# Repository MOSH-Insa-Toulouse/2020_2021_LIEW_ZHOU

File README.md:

# TP MOSH Gas Sensor Application using LoRa Communication
This project is done in conjunction with the Smart Devices module. The objective of this project is to develop an application that acts as a breathalyser, detecting alcohol and send a warning to, for example, a web application. The communication from the sensor node to that web application was done through The Things Network platform via LoRa. We created a graphical interface at Node-RED to visualise the gas sensor value.

## Arduino
For the prototyping on Arduino, we did not use the gas sensor fabricated at the cleanroom but a similar one, namely, MQ3. For energy efficiency purpose, we put the mcu to sleep when no alcohol is detected, and only wake up and transmit using LoRa when alcohol is detected (gas sensor value exceeds a certain threshold).

### Materials

Following is a list of the components used:
* Arduino Uno x 1 
* RN2483A LoRa module x 1
* LED x 1
* Gas sensor MQ3 x 1

### LoRa Communication through TTN

### Graphical Interface (Node-RED)

## Datasheet
Click [here](https://github.com/MOSH-Insa-Toulouse/2020_2021_LIEW_ZHOU/blob/main/Datasheet.pdf) to see the datasheet we created for the gas sensor we fabricated at the cleanroom training. 

## KiCad - Shield for Arduino

### TODO design an electronic card with Kicad
- [x] Creat Kicad porject(Gas_sensor_shield)
- [x] Design the circuit board
- [x] Verification of electrical tests **ERC**
- [x] Association of component footprints with their case
- [x] Netlist generation
- [x] Design of the electronic card
- [x] Importing the netlist
- [x] Component placement
- [x] Define the design constraints of the electronic board ([stackup](https://www.emsproto.com/fr/standard-multi-layer-pcb-stackup))
- [x] Route the tracks of the electronic board

### Schematic

### Placement and Routing

### 3D View

## LTSpice
### Objective
This gas sensor gives an output of around 100 nA. This is not acceptable for normal microcontrollers used nowadays. Therefore, to obtain the output of the gas sensor, the following circuit is needed as an intermediate between the gas sensor and the ADC of  a microcontroller. This circuit will give a gain of 100 in nominal condition.

## Contribution
### Students 
* Terence Chun Heng LIEW
* Zheng ZHOU
### Tutors
* Jérémie GRISOLIA
* Arnauld BIGANZOLI 
* Benjamin MESTRE

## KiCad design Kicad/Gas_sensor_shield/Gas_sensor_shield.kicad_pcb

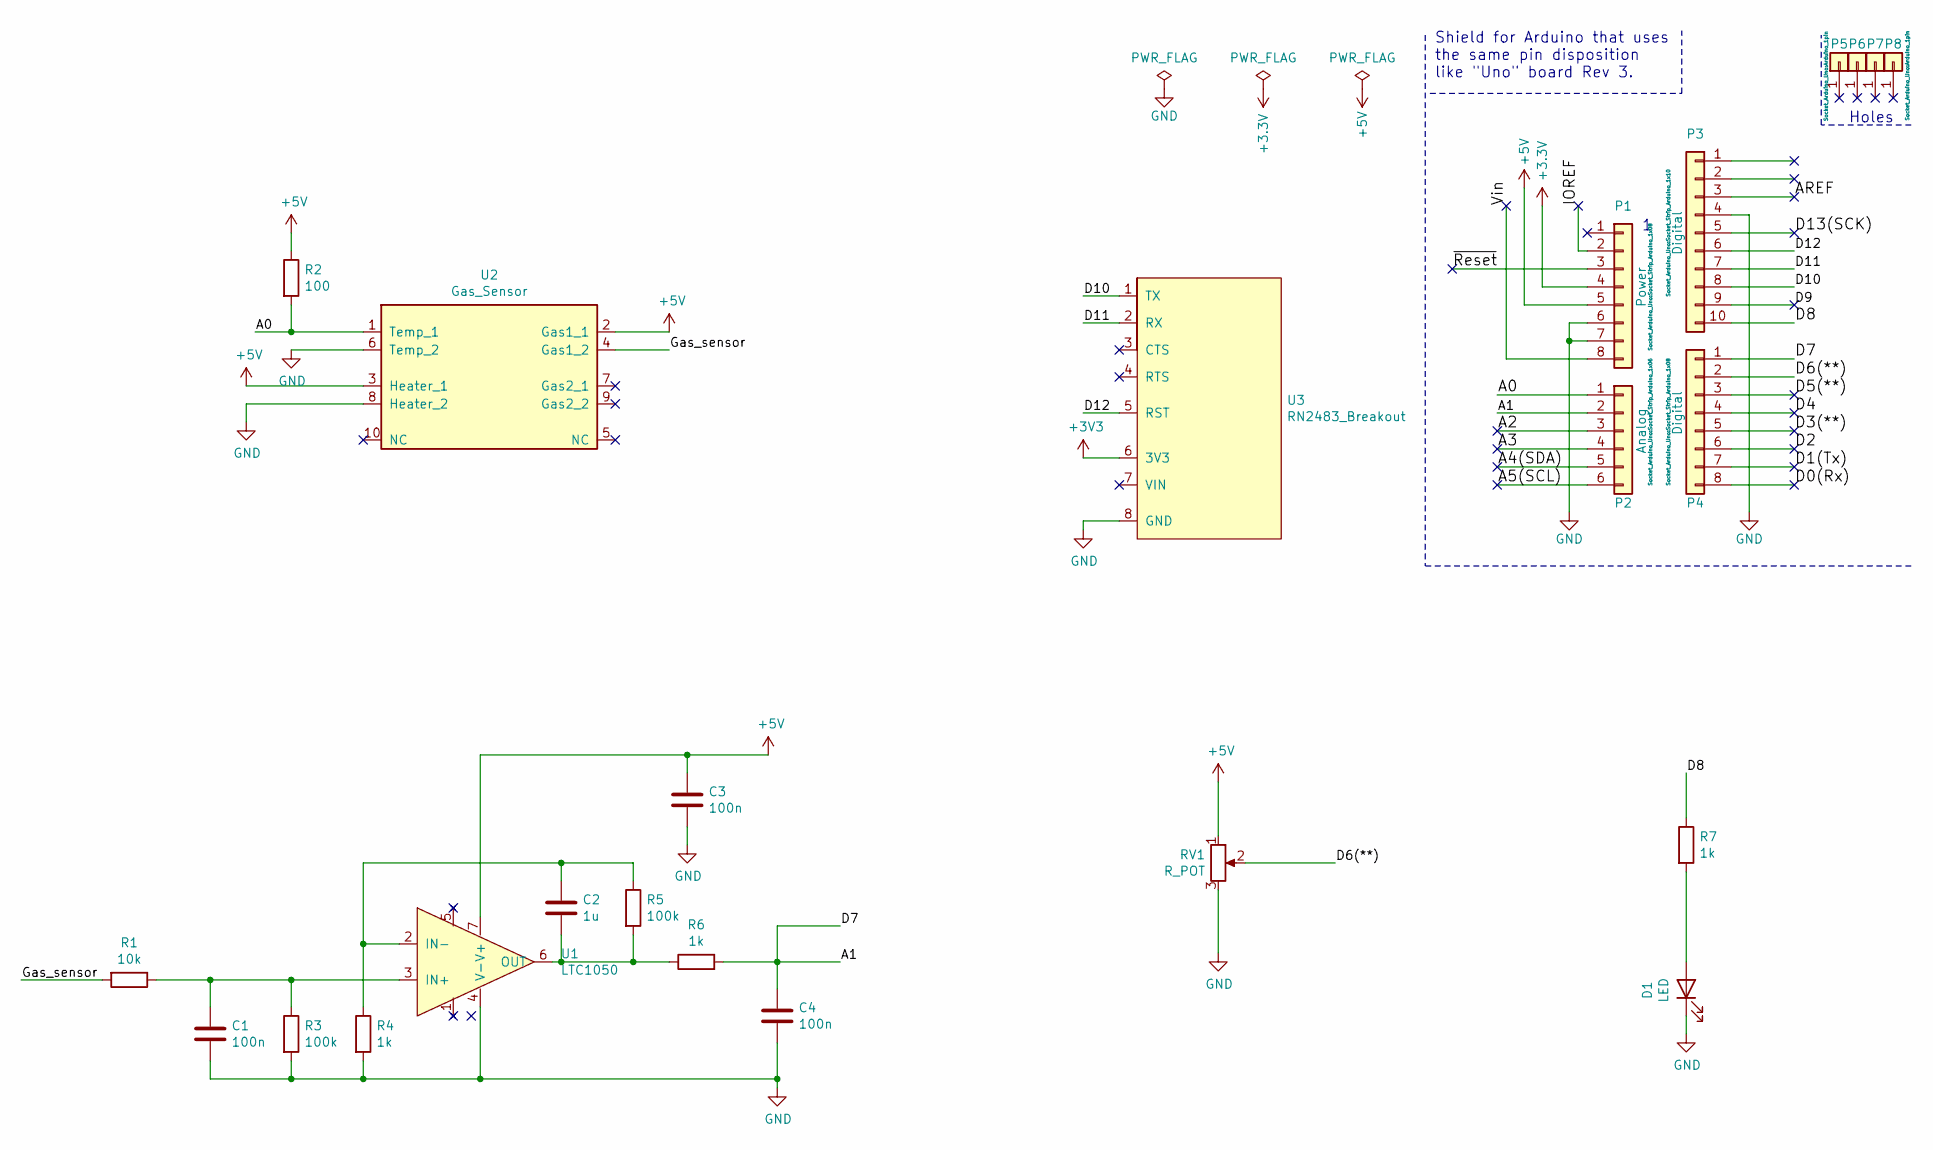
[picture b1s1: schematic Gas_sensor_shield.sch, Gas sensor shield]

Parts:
C1, C3, C4: 100n; CP_Radial_D5.0mm_P2.00mm
C2: 1u; CP_Radial_D5.0mm_P2.00mm
D1: LED; LED_D3.0mm
P1: Power; Socket_Strip_Arduino_1x08
P2: Analog; Socket_Strip_Arduino_1x06
P3: Digital; Socket_Strip_Arduino_1x10
P4: Digital; Socket_Strip_Arduino_1x08
P5, P6, P7, P8: CONN_01X01; Arduino_1pin
R1: 10k; R_Axial_DIN0204_L3.6mm_D1.6mm_P7.62mm_Horizontal
R2: 100; R_Axial_DIN0204_L3.6mm_D1.6mm_P7.62mm_Horizontal
R3, R5: 100k; R_Axial_DIN0204_L3.6mm_D1.6mm_P7.62mm_Horizontal
R4, R6, R7: 1k; R_Axial_DIN0204_L3.6mm_D1.6mm_P7.62mm_Horizontal
RV1: R_POT; Potentiometer_ACP_CA9-V10_Vertical
U1: LTC1050
U2: Gas_Sensor; Sensor_gas
U3: RN2483_Breakout; RN2483_breakout

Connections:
+5V: C3.1, P1.5, R2.1, RV1.1, U1.7 (V+), U2.2 (Gas1_1), U2.3 (Heater_1)
/A0: P2.1, R2.2, U2.1 (Temp_1)
/A1: C4.1, P2.2, P4.1, R6.2
/A2: P2.3
/A3: P2.4
/A4(SDA): P2.5
/A5(SCL): P2.6
/AREF: P3.3
/D0(Rx): P4.8
/D1(Tx): P4.7
/D2: P4.6
/D3(**): P4.5
/D4: P4.4
/D5(**): P4.3
/D6(**): P4.2, RV1.2
/D8: P3.10, R7.1
/D9: P3.9
/D10: P3.8, U3.1 (TX)
/D11: P3.7, U3.2 (RX)
/D12: P3.6, U3.5 (RST)
/D13(SCK): P3.5
/Gas_sensor: R1.2, U2.4 (Gas1_2)
/IOREF: P1.2
/Vin: P1.8
/~Reset~: P1.3
GND: C1.2, C3.2, C4.2, D1.1 (K), P1.6, P1.7, P3.4, R3.2, R4.2, RV1.3, U1.4 (V-), U2.6 (Temp_2), U2.8 (Heater_2), U3.8 (GND)
unnamed: C1.1, R1.1, R3.1, U1.3 (IN+)
unnamed: C2.1, R4.1, R5.1, U1.2 (IN-)
unnamed: C2.2, R5.2, R6.1, U1.6 (OUT)
unnamed: D1.2 (A), R7.2

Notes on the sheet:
Shield for Arduino that uses the same pin disposition like "Uno" board Rev 3.
Holes

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
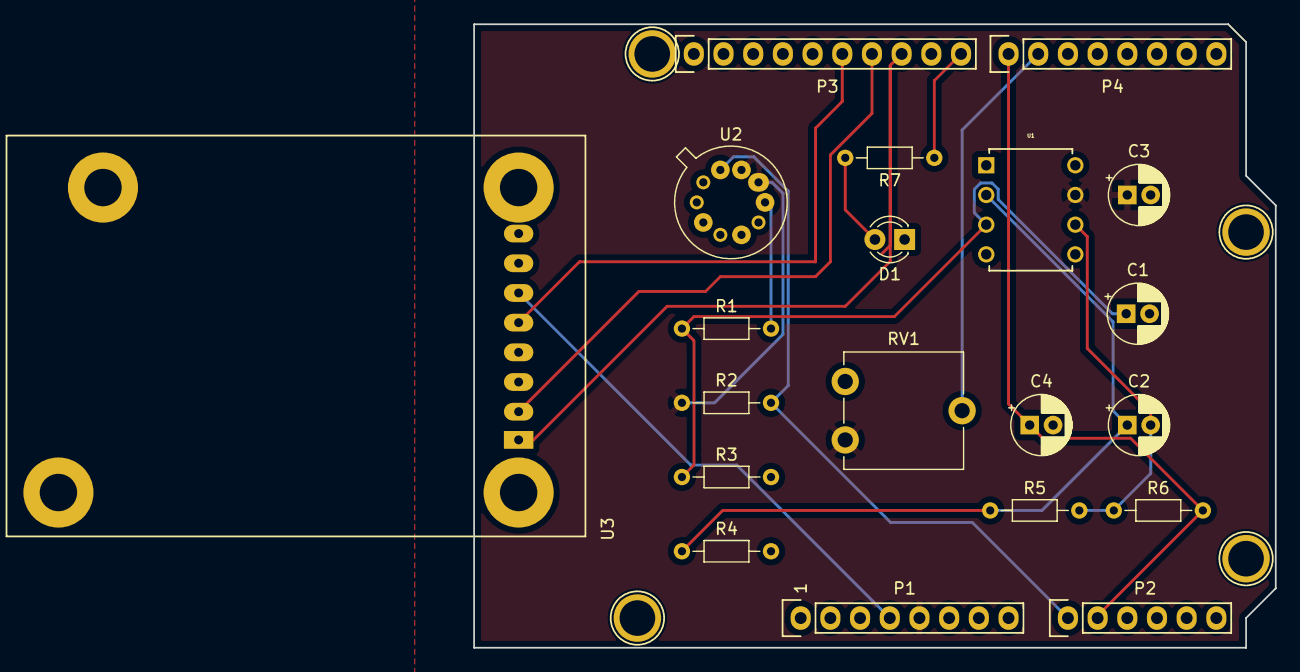
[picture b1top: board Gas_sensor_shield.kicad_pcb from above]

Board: 2 copper layers, 68.6 x 53.3 mm, 24 parts (0 on the bottom side), 15 nets.

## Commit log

2020-12-11 modified lora and deleted README.md
2020-12-11 analog interrupt works
2020-12-11 energy friendly firmware done, put cpu to sleep and only transmit to TTN when alcohol is detected
2020-12-13 added Kicad Project
2020-12-13 Modified Readme
2020-12-13 Added Design of the circuit board
2020-12-13 Added the design of the electronic card
2020-12-13 modified the circuit board and routed
2020-12-13 added few lines on readme
2020-12-22 added images of kicad
2020-12-22 modified routing
2021-01-15 modify datasheet
2021-01-16 modify small error in README
